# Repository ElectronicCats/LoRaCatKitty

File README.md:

# LoRa Cat: Kitty

Electronic Cats invests time and resources providing this open source design, please support Electronic Cats and open-source hardware by purchasing products from Electronic Cats!

Designed by Electronic Cats.

Firmware released under an GNU AGPL v3.0 license. See the LICENSE file for more information.

Hardware released under an CERN Open Hardware Licence v1.2. See the LICENSE_HARDWARE file for more information.

Electronic Cats is a registered trademark, please do not use if you sell these PCBs.

23 Nov 2016

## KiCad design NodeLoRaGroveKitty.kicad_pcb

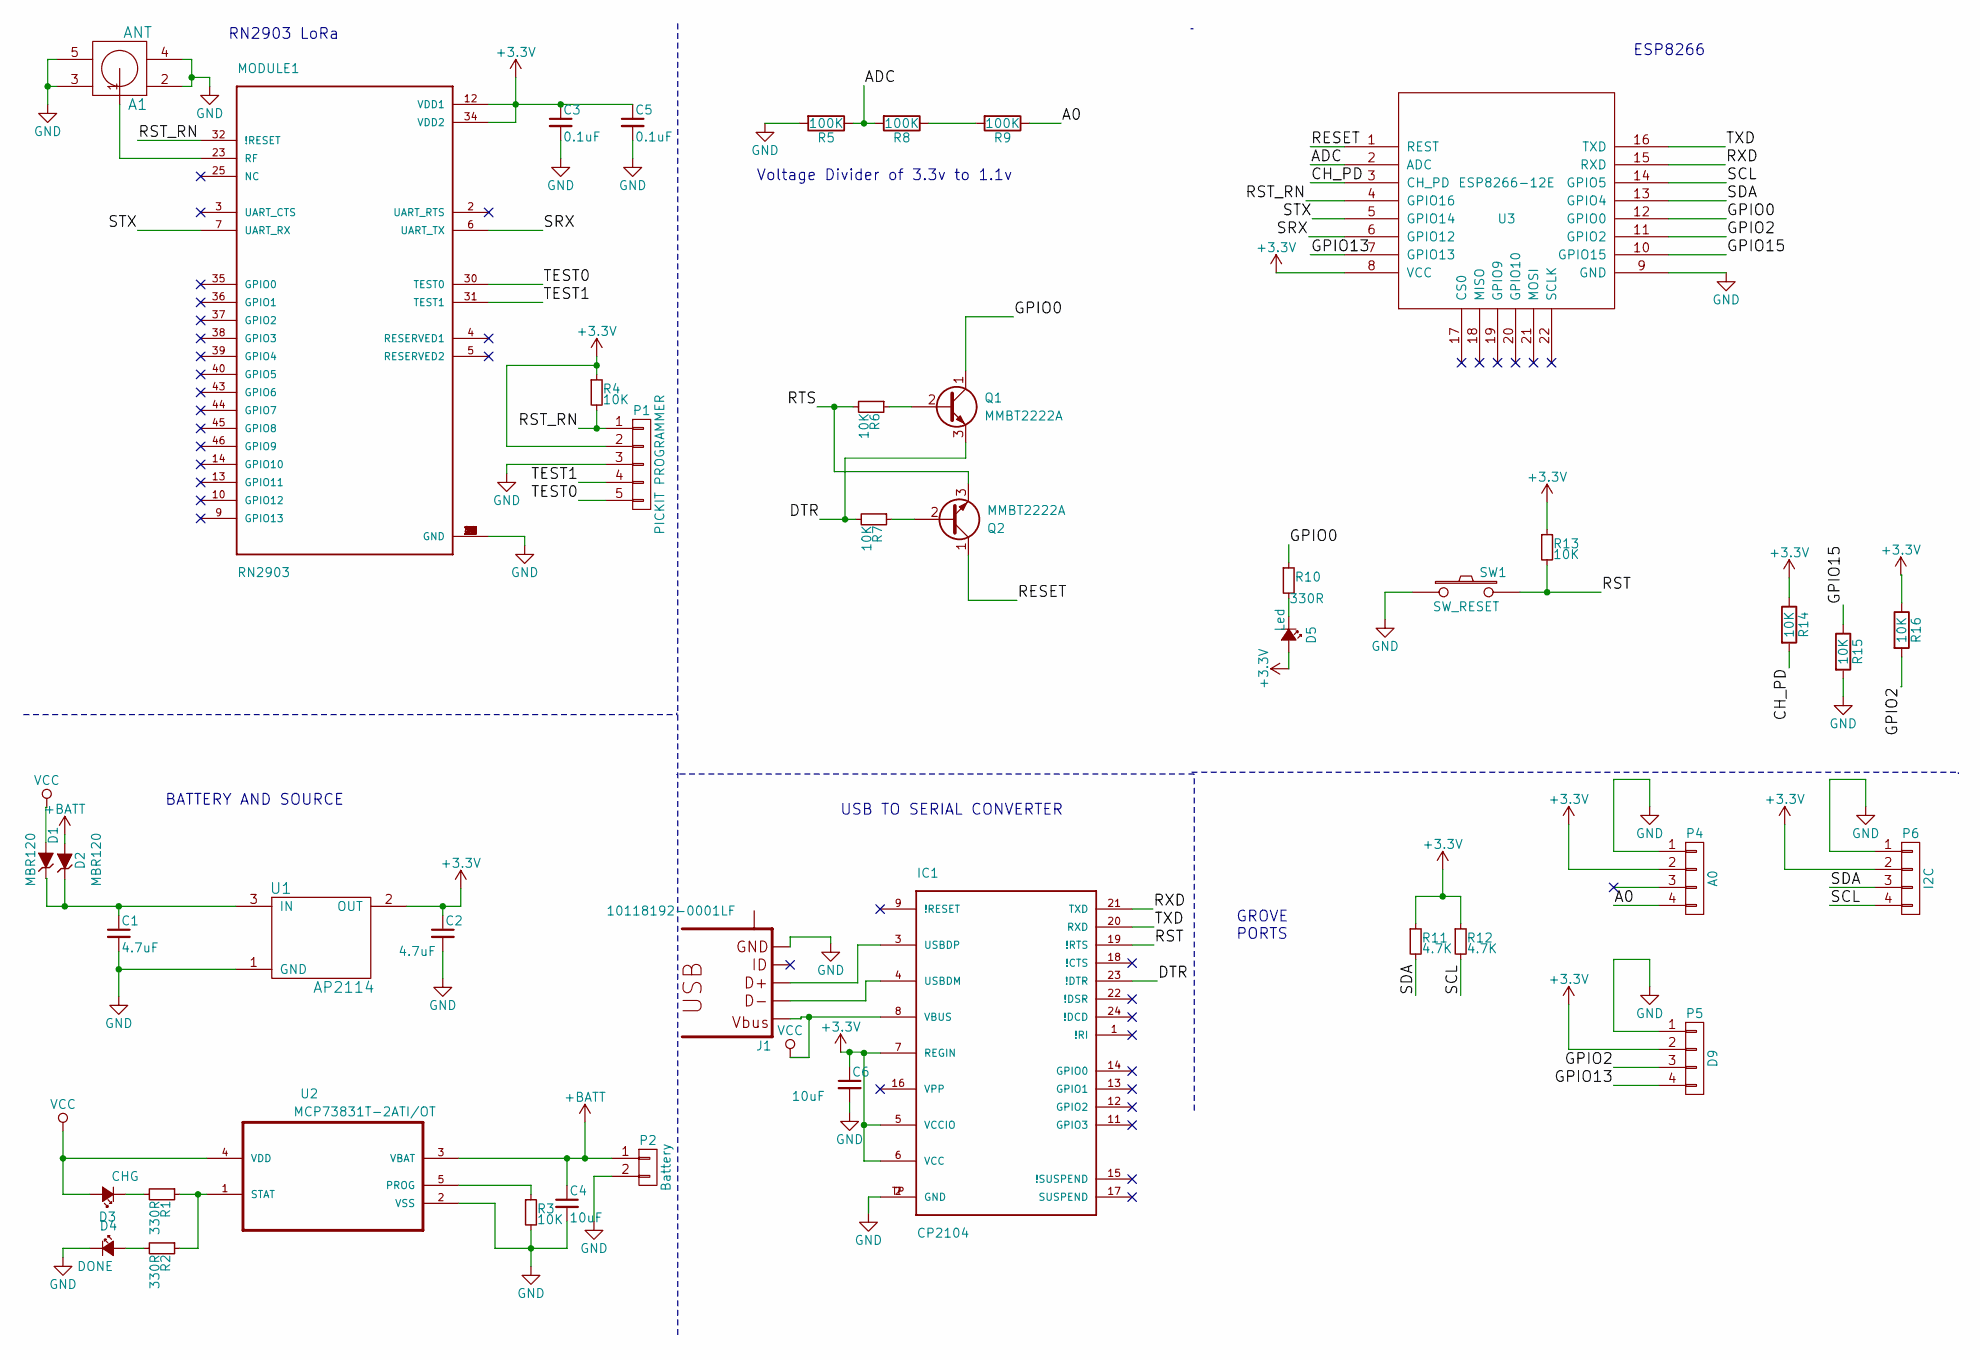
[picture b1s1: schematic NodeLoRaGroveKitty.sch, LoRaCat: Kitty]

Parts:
A1: ANT; SMA_Conn_Ant
C1, C2: 4.7uF; C_0805_HandSoldering
C3, C5: 0.1uF; C_0805_HandSoldering
C4, C6: 10uF; C_0805_HandSoldering
D1, D2: MBR120; D_SOD-123
D3: CHG; LED_0805
D4: DONE; LED_0805
D5: Led; LED_0805
IC1: CP2104; QFN-24_4x4mm_Pitch0.5mm_NoMask
J1: 10118192-0001LF
MODULE1: RN2903; RN2483
P1: PICKIT PROGRAMMER; Pin_Header_Straight_1x05_Pitch2.54mm
P2: Battery; panelmate_smd_2
P4: A0; JST_PH_S4B-PH-SM4-TB_04x2.00mm_Angled
P5: D9; JST_PH_S4B-PH-SM4-TB_04x2.00mm_Angled
P6: I2C; JST_PH_S4B-PH-SM4-TB_04x2.00mm_Angled
Q1, Q2: MMBT2222A; SOT-23
R1, R2, R10: 330R; R_0805_HandSoldering
R3, R4, R6, R7, R13, R14, R15, R16: 10K; R_0805_HandSoldering
R5, R8, R9: 100K; R_0805_HandSoldering
R11, R12: 4.7K; R_0805_HandSoldering
SW1: SW_RESET; SW_SPST_B3U-1000P
U1: AP2114; SOT-223-3Lead_TabPin2
U2: MCP73831T-2ATI/OT; SOT-23-5
U3: ESP8266-12E; ESP-12E

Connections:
+3V3: C2.1, C3.1, C5.1, C6.1, D5.2 (A), IC1.5 (VCCIO), IC1.6 (VCC), IC1.7 (REGIN), MODULE1.12 (VDD1), MODULE1.34 (VDD2), P1.2, P4.2, P5.2, P6.2, R4.1, R11.1, R12.1, R13.1, R14.1, R16.1, U1.2 (OUT), U3.8 (VCC)
+BATT: C4.1, D2.2 (A), P2.1, U2.3 (VBAT)
/A0: P4.4, R9.1
/ADC: R5.1, R8.2, U3.2 (ADC)
/CH_PD: R14.2, U3.3 (CH_PD)
/DTR: IC1.23 (!DTR), Q1.3 (E), R7.2
/GPIO0: Q1.1 (C), R10.1, U3.12 (GPIO0)
/GPIO2: P5.3, R16.2, U3.11 (GPIO2)
/GPIO13: P5.4, U3.7 (GPIO13)
/GPIO15: R15.1, U3.10 (GPIO15)
/RESET: Q2.1 (C), U3.1 (REST)
/RST: IC1.19 (!RTS), R13.2, SW1.2; also elsewhere on the board
/RST_RN: MODULE1.32 (!RESET), P1.1, R4.2, U3.4 (GPIO16)
/RTS: Q2.3 (E), R6.2
/RXD: IC1.21 (TXD), U3.15 (RXD)
/SCL: P6.4, R12.2, U3.14 (GPIO5)
/SDA: P6.3, R11.2, U3.13 (GPIO4)
/SRX: MODULE1.6 (UART_TX), U3.6 (GPIO12)
/STX: MODULE1.7 (UART_RX), U3.5 (GPIO14)
/TEST0: MODULE1.30 (TEST0), P1.5
/TEST1: MODULE1.31 (TEST1), P1.4
/TXD: IC1.20 (RXD), U3.16 (TXD)
GND: A1.2, A1.3, A1.4, A1.5, C1.2, C2.2, C3.2, C4.2, C5.2, C6.2, D4.1 (K), IC1.2 (GND), IC1.TP (GND), J1.5 (GND), MODULE1.1 (GND), MODULE1.8 (GND), MODULE1.11 (GND), MODULE1.20 (GND), MODULE1.21 (GND), MODULE1.22 (GND), MODULE1.24 (GND), MODULE1.26 (GND), MODULE1.27 (GND), MODULE1.28 (GND), MODULE1.33 (GND), MODULE1.41 (GND), MODULE1.47 (GND), P1.3, P2.2, P4.1, P5.1, P6.1, R3.2, R5.2, R15.2, SW1.1, U1.1 (GND), U2.2 (VSS), U3.9 (GND); also elsewhere on the board
unnamed: A1.1, MODULE1.23 (RF)
unnamed: C1.1, D1.1 (K), D2.1 (K), U1.3 (IN)
unnamed: D3.1 (K), R1.2
unnamed: D4.2 (A), R2.2
unnamed: D5.1 (K), R10.2
unnamed: IC1.3 (USBDP), J1.3 (D+)
unnamed: IC1.4 (USBDM), J1.2 (D-)
unnamed: J1.M1 (S), J1.M2 (S), J1.S1 (S), J1.S2 (S), J1.S3 (S), J1.S4 (S)
unnamed: Q1.2 (B), R6.1
unnamed: Q2.2 (B), R7.1
unnamed: R1.1, R2.1, U2.1 (STAT)
unnamed: R3.1, U2.5 (PROG)
unnamed: R8.1, R9.2
VCC: D1.2 (A), D3.2 (A), IC1.8 (VBUS), J1.1 (VBUS), U2.4 (VDD)

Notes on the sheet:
RN2903 LoRa
ESP8266
GROVE PORTS
BATTERY AND SOURCE
Voltage Divider of 3.3v to 1.1v
USB TO SERIAL CONVERTER

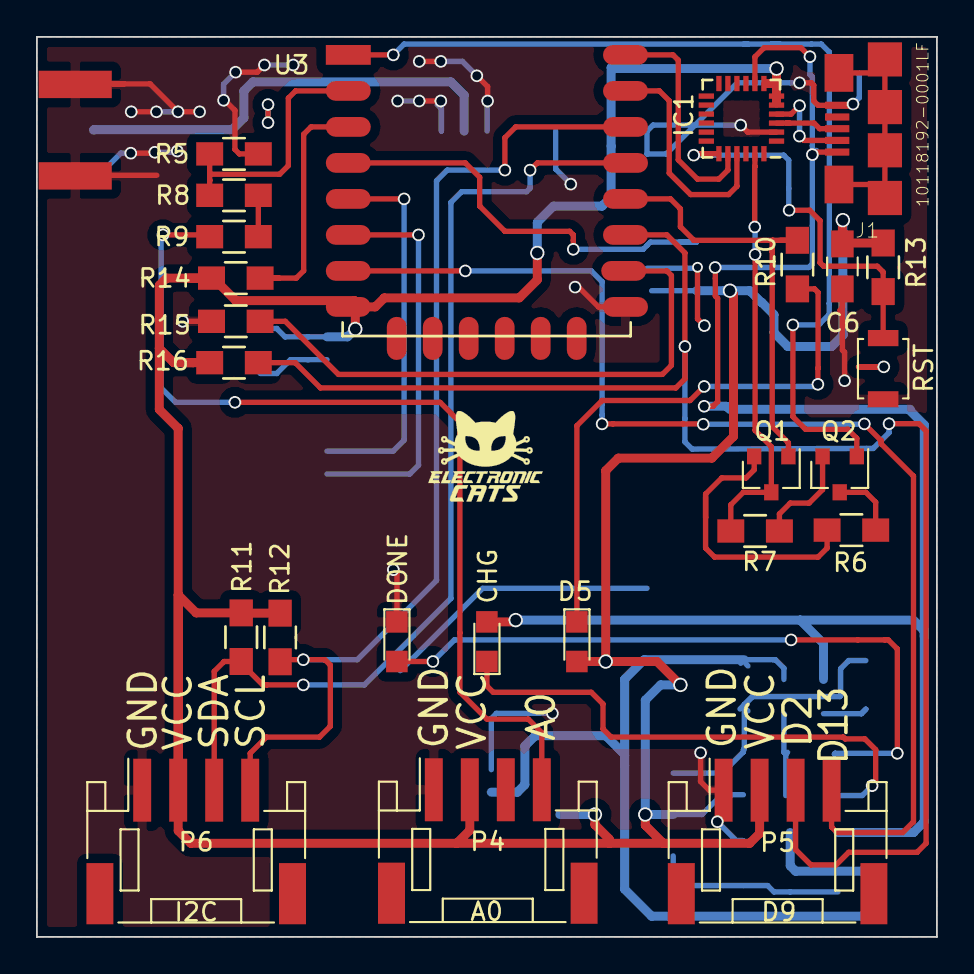
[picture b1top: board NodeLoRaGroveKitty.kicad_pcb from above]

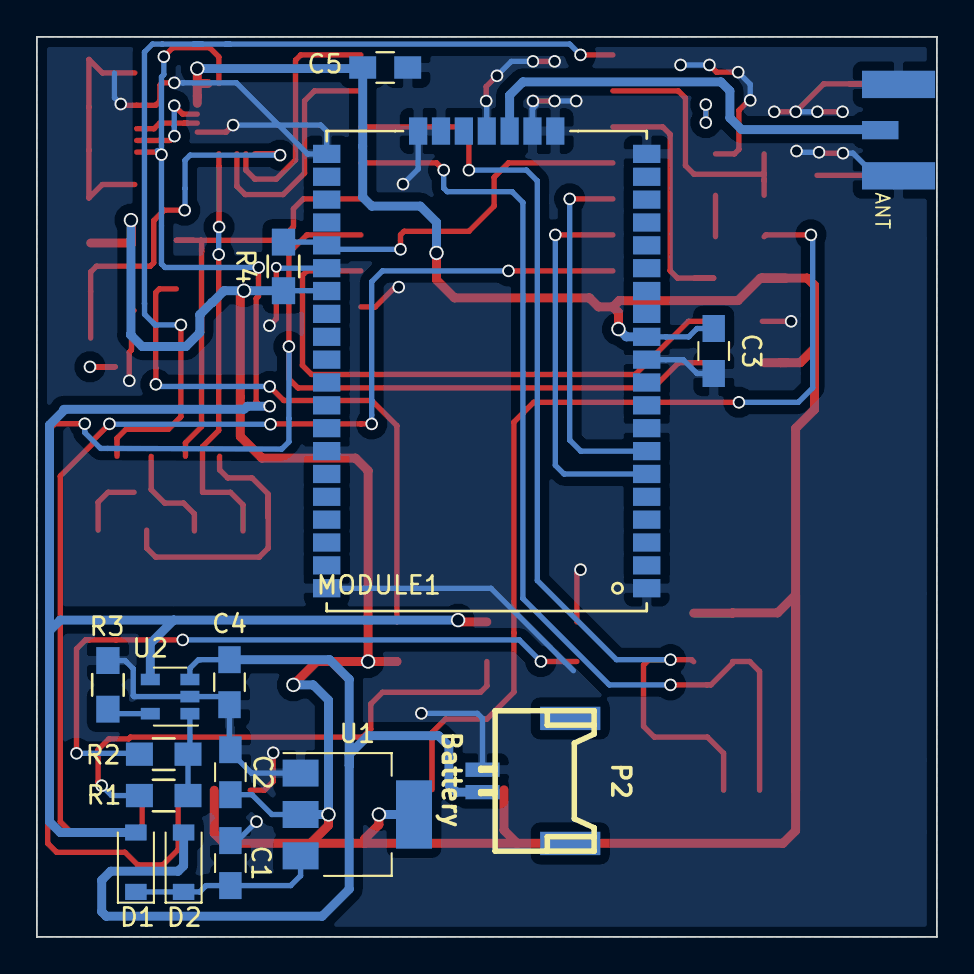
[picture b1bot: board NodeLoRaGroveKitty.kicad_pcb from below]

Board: 2 copper layers, 50.0 x 50.0 mm, 41 parts (16 on the bottom side), 35 nets.

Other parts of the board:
RST: SW_RESET; SW_SPST_B3U-1000P

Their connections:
/RST: RST.2; also elsewhere on the board
GND: RST.1; also elsewhere on the board

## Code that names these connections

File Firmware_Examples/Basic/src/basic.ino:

/*
 * Author: JP Meijers
 * Date: 2016-10-20
 *
 * Transmit a one byte packet via TTN. This happens as fast as possible, while still keeping to
 * the 1% duty cycle rules enforced by the RN2483's built in LoRaWAN stack. Even though this is
 * allowed by the radio regulations of the 868MHz band, the fair use policy of TTN may prohibit this.
 *
 * CHECK THE RULES BEFORE USING THIS PROGRAM!
 *
 * CHANGE ADDRESS!
 * Change the device address, network (session) key, and app (session) key to the values
 * that are registered via the TTN dashboard.
 * The appropriate line is "myLora.initABP(XXX);" or "myLora.initOTAA(XXX);"
 * When using ABP, it is advised to enable "relax frame count".
 *
 * Connect the RN2xx3 as follows:
 * RN2xx3 -- ESP8266
 * Uart TX -- GPIO4
 * Uart RX -- GPIO5
 * Reset -- GPIO15
 * Vcc -- 3.3V
 * Gnd -- Gnd
 *
 */
#include <rn2xx3.h>
#include <SoftwareSerial.h>

#define RESET 15
SoftwareSerial mySerial(4, 5); // RX, TX !! labels on relay board is swapped !!

//create an instance of the rn2xx3 library,
//giving the software UART as stream to use,
//and using LoRa WAN
rn2xx3 myLora(mySerial);

// the setup routine runs once when you press reset:
void setup() {
  // LED pin is GPIO2 which is the ESP8266's built in LED
  pinMode(2, OUTPUT);
  led_on();

  // Open serial communications and wait for port to open:
  Serial.begin(57600);
  mySerial.begin(57600);

  delay(1000); //wait for the arduino ide's serial console to open

  Serial.println("Startup");

  initialize_radio();

  //transmit a startup message
  myLora.tx("TTN Mapper on ESP8266 node");

  led_off();
  delay(2000);
}

void initialize_radio()
{
  //reset RN2xx3
  pinMode(RESET, OUTPUT);
  digitalWrite(RESET, LOW);
  delay(100);
  digitalWrite(RESET, HIGH);

  delay(100); //wait for the RN2xx3's startup message
  mySerial.flush();

  //check communication with radio
  String hweui = myLora.hweui();
  while(hweui.length() != 16)
  {
    Serial.println("Communication with RN2xx3 unsuccesful. Power cycle the board.");
    Serial.println(hweui);
    delay(10000);
    hweui = myLora.hweui();
  }

  //print out the HWEUI so that we can register it via ttnctl
  Serial.println("When using OTAA, register this DevEUI: ");
  Serial.println(hweui);
  Serial.println("RN2xx3 firmware version:");
  Serial.println(myLora.sysver());

  //configure your keys and join the network
  Serial.println("Trying to join TTN");
  bool join_result = false;

  //ABP: initABP(String addr, String AppSKey, String NwkSKey);
  join_result = myLora.initABP("02017201", "8D7FFEF938589D95AAD928C2E2E7E48F", "AE17E567AECC8787F749A62F5541D522");

  //OTAA: initOTAA(String AppEUI, String AppKey);
  //join_result = myLora.initOTAA("70B3D57ED00001A6", "A23C96EE13804963F8C2BD6285448198");

  while(!join_result)
  {
    Serial.println("Unable to join. Are your keys correct, and do you have TTN coverage?");
    delay(60000); //delay a minute before retry
    join_result = myLora.init();
  }
  Serial.println("Successfully joined TTN");

}

// the loop routine runs over and over again forever:
void loop() {
    led_on();

    Serial.println("TXing");
    myLora.tx("!"); //one byte, blocking function

    led_off();
    delay(200);
}

void led_on()
{
  digitalWrite(2, 1);
}

void led_off()
{
  digitalWrite(2, 0);
}

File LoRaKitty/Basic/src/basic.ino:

/*
 * Author: Andres Sabas @ Electronic Cats
 * Date: 2017-01-27
 *
 * Example for LoRa Kitty with OTA and ABP or OTAA LORAWAM
 * Transmit a one byte packet via LoRaWAN. This happens as fast as possible, while still keeping to
 * the 1% duty cycle rules enforced by the RN2xx3's built in LoRaWAN stack. Even though this is
 * allowed by the radio regulations of the 868MHz and 915Mhz band, the fair use policy of LoRaWAN may prohibit this.
 *
 * CHECK THE RULES BEFORE USING THIS PROGRAM!
 *
 * CHANGE ADDRESS!
 * Change the device address, network (session) key, and app (session) key to the values
 * that are registered via the LoRa dashboard.
 * The appropriate line is "myLora.initABP(XXX);" or "myLora.initOTAA(XXX);"
 * When using ABP, it is advised to enable "relax frame count".
 *
 * Connect the RN2xx3 as follows:
 * RN2xx3 -- ESP8266
 * Uart TX -- GPIO12
 * Uart RX -- GPIO14
 * Reset -- GPIO16
 * Vcc -- 3.3V
 * Gnd -- Gnd
 *
 */


#include <rn2xx3.h>
#include <SoftwareSerial.h>
#include <ESP8266WiFi.h>
#include <ESP8266mDNS.h>
#include <WiFiUdp.h>
#include <ArduinoOTA.h>
#include <CayenneLPP.h>

//Use Low Power Payload https://mydevices.com/cayenne/docs/lora/#lora-cayenne-low-power-payload
CayenneLPP lpp(51);

const char* ssid = "TIH-Alpha2.4";
const char* password = "";

#define RESET 16
SoftwareSerial mySerial(12, 14); // RX, TX !! labels on relay board is swapped !!

//create an instance of the rn2xx3 library,
//giving the software UART as stream to use,
//and using LoRa WAN
rn2xx3 myLora(mySerial);

// the setup routine runs once when you press reset:
void setup() {
  // LED pin is GPIO2 which is the ESP8266's built in LED
  pinMode(2, INPUT);

  // Open serial communications and wait for port to open:
  Serial.begin(115200);
  mySerial.begin(57600);

  delay(10); //wait for the arduino ide's serial console to open

  Serial.println("Setup WiFi Connection");

  Serial.println();
  Serial.println();
  Serial.print("Connecting to ");
  Serial.println(ssid);

  WiFi.mode(WIFI_STA);
  WiFi.begin(ssid, password);

  while (WiFi.waitForConnectResult() != WL_CONNECTED) {
    Serial.println("Connection Failed! No WiFi!...");
    //delay(5000);
    //ESP.restart();
    break;
}

/*
while (WiFi.status() != WL_CONNECTED) {
  delay(500);
  Serial.print(".");
}*/

if(WiFi.waitForConnectResult() == WL_CONNECTED) {


    // Port defaults to 8266
    // ArduinoOTA.setPort(8266);

    // Hostname defaults to esp8266-[ChipID]
    // ArduinoOTA.setHostname("myesp8266");

    // No authentication by default
    // ArduinoOTA.setPassword("admin");

    // Password can be set with it's md5 value as well
    // MD5(admin) = 21232f297a57a5a743894a0e4a801fc3
    // ArduinoOTA.setPasswordHash("21232f297a57a5a743894a0e4a801fc3");
/*
    ArduinoOTA.onStart([]() {
      String type;
      if (ArduinoOTA.getCommand() == U_FLASH)
        type = "sketch";
      else // U_SPIFFS
        type = "filesystem";

      // NOTE: if updating SPIFFS this would be the place to unmount SPIFFS using SPIFFS.end()
      Serial.println("Start updating " + type);

    });
    */
    ArduinoOTA.onEnd([]() {
      Serial.println("\nEnd");
    });
    ArduinoOTA.onProgress([](unsigned int progress, unsigned int total) {
      Serial.printf("Progress: %u%%\r", (progress / (total / 100)));
    });
    ArduinoOTA.onError([](ota_error_t error) {
      Serial.printf("Error[%u]: ", error);
      if (error == OTA_AUTH_ERROR) Serial.println("Auth Failed");
      else if (error == OTA_BEGIN_ERROR) Serial.println("Begin Failed");
      else if (error == OTA_CONNECT_ERROR) Serial.println("Connect Failed");
      else if (error == OTA_RECEIVE_ERROR) Serial.println("Receive Failed");
      else if (error == OTA_END_ERROR) Serial.println("End Failed");
    });

    ArduinoOTA.begin();


    Serial.println("Ready");
    Serial.print("IP address: ");
    Serial.println(WiFi.localIP());
}
  //initialize radio LoRa
  initialize_radio();
}

void initialize_radio()
{
  //reset RN2xx3
  pinMode(RESET, OUTPUT);
  digitalWrite(RESET, LOW);
  delay(100);
  digitalWrite(RESET, HIGH);

  delay(100); //wait for the RN2xx3's startup message
  mySerial.flush();

  //check communication with radio
  String hweui = myLora.hweui();
  while(hweui.length() != 16)
  {
    Serial.println("Communication with RN2xx3 unsuccesful. Power cycle the board.");
    Serial.println(hweui);
    delay(10000);
    hweui = myLora.hweui();
  }

  //print out the HWEUI so that we can register it via ttnctl
  Serial.println("When using OTAA, register this DevEUI: ");
  Serial.println(hweui);
  Serial.println("RN2xx3 firmware version:");
  Serial.println(myLora.sysver());

  //configure your keys and join the network
  Serial.println("Trying to join TTN");
  bool join_result = false;

  //ABP: initABP(String addr, String AppSKey, String NwkSKey);
  //join_result = myLora.initABP("26021B7C", "3D016DF9E60F6270890FDC2B753C0E99", "EA40E937CF5592742ECA30DEBC1954E5");

  //OTAA: initOTAA(String AppEUI, String AppKey);
  join_result = myLora.initOTAA("70B3D57EF00062AD", "150C667A235B003361457751594DCAFB");

  while(!join_result)
  {
    Serial.println("Unable to join. Are your keys correct, and do you have TTN coverage?");
    delay(30000); //delay a 30 seg before retry
    join_result = myLora.init();
  }
  Serial.println("Successfully joined TTN");

}

// the loop routine runs over and over again forever:
void loop() {
    ArduinoOTA.handle();
    //Reset buffer of lpp
    lpp.reset();

    //Read button
    read_button();

    //Read light
    read_light();

    Serial.println("Sending Data");
    myLora.txBytes(lpp.getBuffer(), lpp.getSize());

    delay(30000); // delay 30 seg for TTN
}

void read_light(){
  int light = analogRead(0);
  Serial.println(light);
  lpp.addAnalogInput(1, light);
}

void read_button(){
  if(digitalRead(2)==1){
    Serial.println("Button press!");
    lpp.addDigitalInput(2, 1);
  }
  else
  {
    Serial.println("Button NO press");
    lpp.addDigitalInput(2, 0);
  }


}

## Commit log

2016-11-24 Added Squematic
2016-11-24 Added Firmware
2016-11-24 Added PDF squematic
2016-12-06 Fix ADC pin
2016-12-06 Added gitignore
2016-12-13 Added Library footprint
2016-12-13 Update Grove to 5v
2016-12-13 Validate footprints
2016-12-14 Correct to 3.3v, and R10
2016-12-14 Add first PCB design
2016-12-15 Fix pines S_TX and S_RX
2016-12-15 Added Logos
2016-12-15 Added labels pinout
2016-12-16 Change GPIO2
2017-01-02 Add pin reset for RN
    GPIO16
2017-01-02 Fix non-copper area
2017-01-02 Fix label's
2017-01-03 Add resistence and pin reset
2017-01-03 Add res and rst pin PCB and Label's
2017-01-03 Update logos
2017-01-04 Fix bug footprint
2017-01-04 Fix re-bug
2017-01-10 Update BOM
2017-01-27 Update Example
2017-01-28 Change to AP2114
2017-01-28 Update ignore
2017-02-01 Add mbr120
2017-02-01 Change Led to GPIO0
2017-02-01 Update gitignore
2017-02-01 Modification for Huzzah and OTA
2017-02-06 Firmware
2017-02-06 Add library for SoftwareSerial
2017-02-08 Fix Rename pin D15 to D2
2017-02-11 Change D2 for D13
2017-02-16 Added autoreset and USB_Serial
2017-02-16 Version 0.5
2017-02-19 Update AP2114, fix bugs JST
2017-02-19 New design PCB
2017-02-21 PCB 1.0v
2017-02-21 Update Labels
2017-02-21 Update inverter label
2017-02-21 Update cache lib
2017-04-12 Change USB with libraries
2017-04-14 Add #maf to battery conector
2017-04-19 Update configuration
2017-05-03 Add new RN and fix ways
2017-05-03 Fix gnd
2017-06-14 checksum
2017-07-10 fix connects
2017-07-11 Added LLP, read button and light sensor
2017-07-12 Work with TTN and Cayenne
2017-07-12 Rename folder examples
2017-07-12 Rename folder KicadLibrary
2017-07-15 Add gitignore pioeventes
